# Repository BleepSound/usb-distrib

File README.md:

[![CC BY-SA 4.0][cc-by-sa-shield]][cc-by-sa]

# USB distribution board

Latest documentation available at https://bleepsound.github.io/modules/

This work is licensed under a
[Creative Commons Attribution-ShareAlike 4.0 International License][cc-by-sa].

[![CC BY-SA 4.0][cc-by-sa-image]][cc-by-sa]

[cc-by-sa]: http://creativecommons.org/licenses/by-sa/4.0/
[cc-by-sa-image]: https://licensebuttons.net/l/by-sa/4.0/88x31.png
[cc-by-sa-shield]: https://img.shields.io/badge/License-CC%20BY--SA%204.0-lightgrey.svg

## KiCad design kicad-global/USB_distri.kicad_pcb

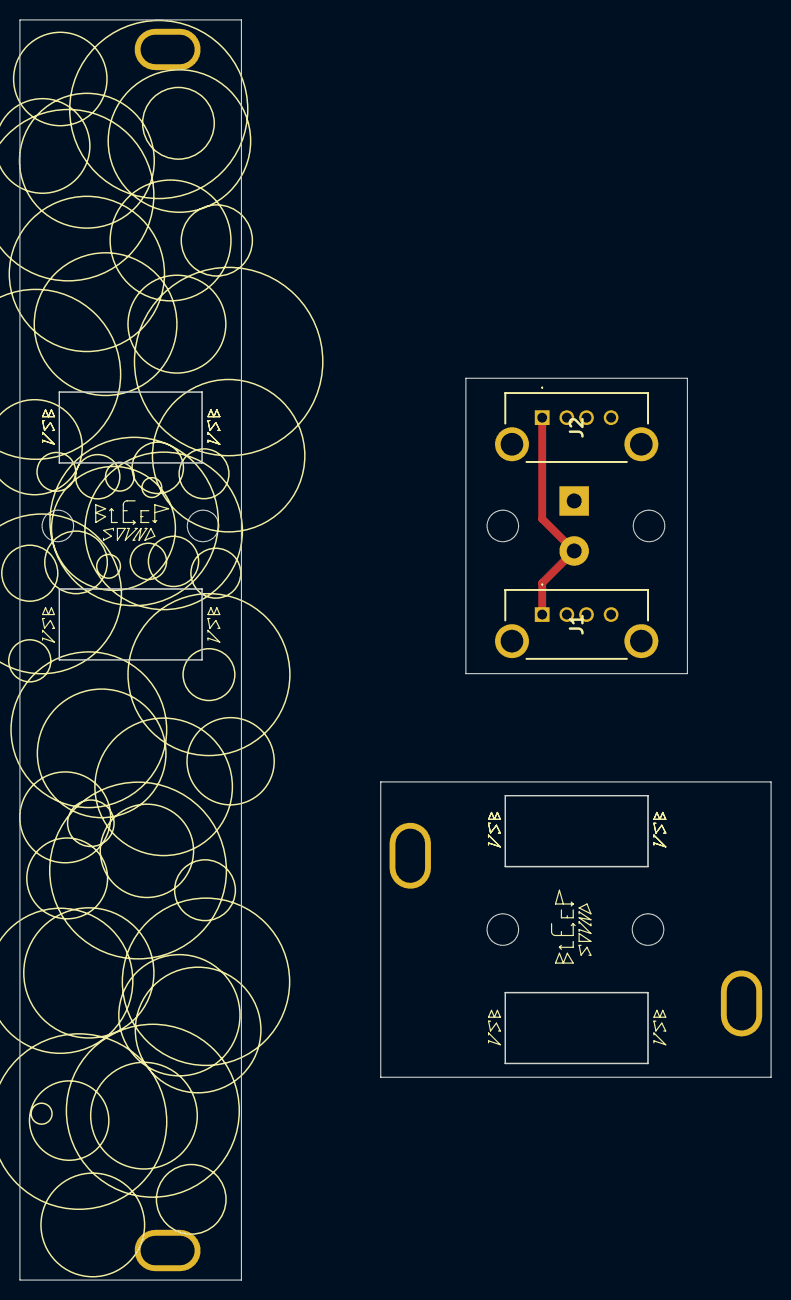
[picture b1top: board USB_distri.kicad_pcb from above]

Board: 2 copper layers, 76.3 x 128.0 mm, 13 parts (1 on the bottom side), 2 nets.

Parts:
H1, H2, H3, H4: MountingHole; Doepfer Mounting hole
H5, H6, H7, H8, H9, H10: SpacerHoles; MountingHole_3.2mm_M3
J1, J2: GSB11111ALF
J3: Power_Input; TerminalBlock_bornier-2_P5.08mm

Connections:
+5V: J1.1 (5V), J2.1 (5V), J3.2
GND: J1.2 (D-), J1.3 (D+), J1.4 (GND), J1.MH1, J1.MH2, J2.2 (D-), J2.3 (D+), J2.4 (GND), J2.MH1, J2.MH2, J3.1

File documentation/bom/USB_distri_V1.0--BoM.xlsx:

USB_distri_V1.0 Bill of Materials
Schematic: | USB_distri | Component Groups: | 2
Variant: | default | Component Count: | 3 (0 SMD/ 3 THT)
Revision: | 1.0 | Fitted Components: | 3 (0 SMD/ 3 THT)
Date: | 2023-10-13 | Number of PCBs: | 1
KiCad Version: | 7.0.7-7.0.7~ubuntu22.04.1 | Total Components: | 3
Row | Description | References | Value | Quantity Per PCB | Comments
1 | USB Connectors USB 2.0, Type A, Receptacle, Vertical, 4 Pins, Shell with Nickel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 | J1 J2 | GSB11111ALF | 2
2 | Generic screw terminal, single row, 01x02, script generated (kicad-library-util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 | J3 | Power_Input | 1

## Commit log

2023-10-15 V1.0 first commit, all doc included
2023-10-15 update silkscreen with info on polarity + readme
2025-11-27 add licence
